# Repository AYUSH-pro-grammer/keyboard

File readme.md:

# keyboard

Custom mechanical keyboard PCB designed using KiCad.

###Motivation

I designed this device in order to get some practical experience in hardware design, PCB manufacturing, and embedded systems programming. Instead of using an off-the-shelf keyboard design, I aimed at learning all the steps required to manufacture a custom keyboard.

Working on this project, I had the opportunity to do schematic design, PCB layouting, components selection, 3D rendering, firmware writing, and manufacturing preparation with the help of KiCad. Thus, having successfully completed the whole design cycle, I got some practical experience in both hardware and software engineering.

It was my intention not only to manufacture a working device but also learn some electronics designing techniques along with problem solving in the engineering field while doing a project that is manufacturable and improvable in the future.

### Build Looks 

## Images

### Schematic

### PCB

### PCB Front 3D

### PCB Back 3D

### 3D Model 1
## Features

### 3D Model 2

---

- Custom Keyboard PCB
- Designed in KiCad
- 3D PCB Visualization
- Gerber Manufacturing Files Included

---

## Repository Structure

```text
keyboard/
│
├── code/
├── image/
├── kicad/
├── grb.zip
└── README.md
```

---

## Files

- `code/` → Firmware / keyboard code
- `image/` → PCB renders and 3D models
- `kicad/` → KiCad project files
- `grb.zip` → Gerber files for PCB manufacturing

---

## Bill of Materials

| Name | Purpose | Quantity | Avg Cost (USD) | Distributor |
|------|----------|----------|----------|----------|
| Cherry MX2A Switch Set | Key switches for typing | 1 Set | $42.00 | Keychron |
| PBT Keycap Set | Keycaps for switches | 1 Set | $13.00 | Meckeys |
| Raspberry Pi Pico | Keyboard microcontroller | 1 | $5.00 | Robu.in |
| Rotary Encoder (EC11) | Volume/media control knob | 1 | $2.00 | Robu.in |
| Encoder Knob | Mounts on rotary encoder | 1 | $1.00 | Robu.in |
| 1N4148 Diodes | Key matrix isolation | 70–100 | $3.00 | Robu.in |
| PCB Fabrication | Custom keyboard PCB | 1 | $25.00 | JLCPCB / PCBWay |
| PCB Components | Headers, sockets, passive components | 1 Lot | $5.00 | Robu.in |
| MX Hotswap Sockets (Optional) | Tool-free switch replacement | 70 | $15.00 | Meckeys / StackKB |
| USB-C Cable | Connection to computer | 1 | $3.00 | Robu.in |
| Stabilizers | Support for larger keys | 1 Set | $10.00 | Meckeys |
| Screws & Standoffs | Assembly hardware | 1 Lot | $3.00 | Local Supplier |
| 3D Printed Case | Keyboard enclosure | 1 | $20.00 | Local 3D Printing Service |
| 3D Printed Encoder Knob (Optional) | Custom encoder knob | 1 | $1.00 | Local 3D Printing Service |

## Estimated Total

**Recommended Hotswap Build Total: ~$144 USD**

## Author

Created by [AYUSH-pro-grammer](https://github.com/AYUSH-pro-grammer)

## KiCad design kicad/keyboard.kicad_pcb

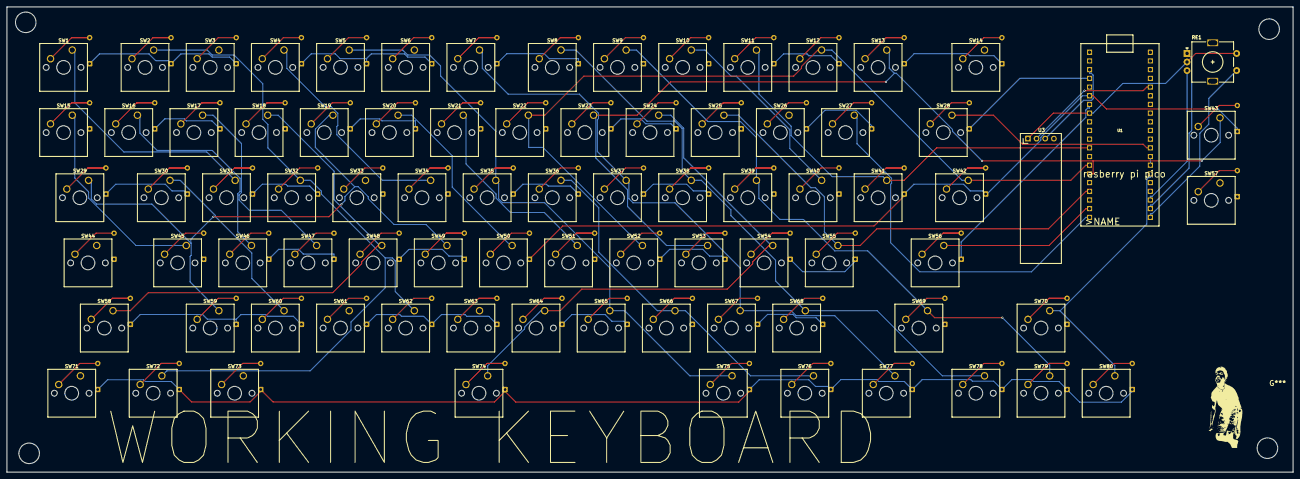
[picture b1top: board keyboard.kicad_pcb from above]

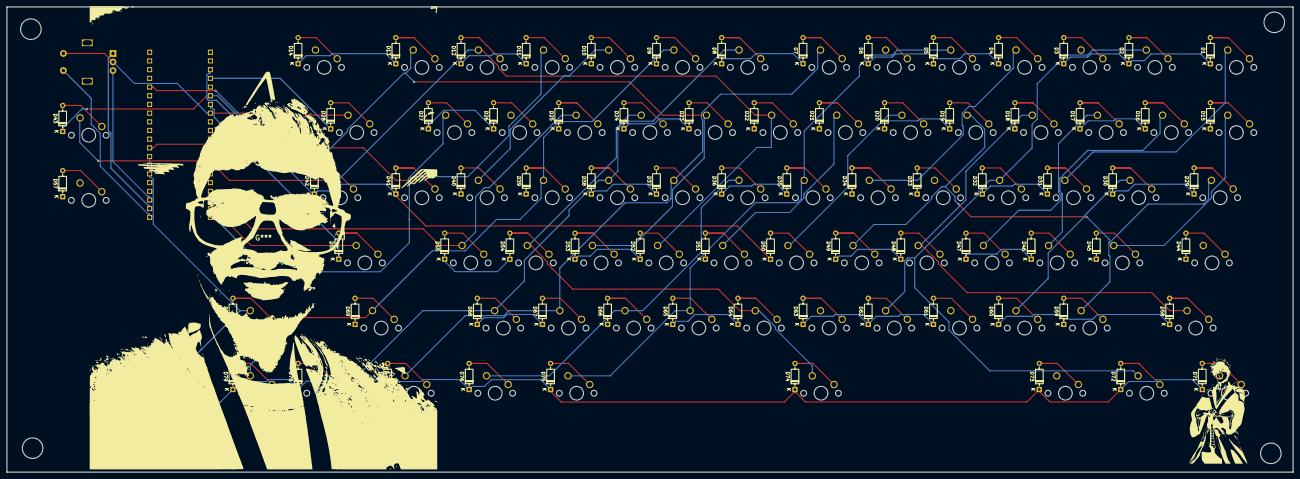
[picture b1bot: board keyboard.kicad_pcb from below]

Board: 2 copper layers, 376.0 x 136.0 mm, 164 parts (81 on the bottom side), 105 nets.

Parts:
D1, D2, D3, D4, D5, D6, D7, D8, D9, D10, D11, D12, D13, D14, D15, D16, D17, D18, D19, D20, D21, D22, D23, D24, D25, D26, D27, D28, D29, D30, D31, D32, D33, D34, D35, D36, D37, D38, D39, D40, D41, D42, D43, D44, D45, D46, D47, D48, D49, D50, D51, D52, D53, D54, D55, D56, D57, D58, D59, D60, D61, D62, D63, D64, D65, D66, D67, D68, D69, D70, D71, D72, D73, D74, D75, D76, D77, D78, D79, D80: 1N914; D_DO-35_SOD27_P7.62mm_Horizontal
RE1: RotaryEncoder_Switch; RotaryEncoder_Alps_EC11E-Switch_Vertical_H20mm
SW1, SW2, SW3, SW4, SW5, SW6, SW7, SW8, SW9, SW10, SW11, SW12, SW13, SW14, SW15, SW16, SW17, SW18, SW19, SW20, SW21, SW22, SW23, SW24, SW25, SW26, SW27, SW28, SW29, SW30, SW31, SW32, SW33, SW34, SW35, SW36, SW37, SW38, SW39, SW40, SW41, SW42, SW43, SW44, SW45, SW46, SW47, SW48, SW49, SW50, SW51, SW52, SW53, SW54, SW55, SW56, SW57, SW58, SW59, SW60, SW61, SW62, SW63, SW64, SW65, SW66, SW67, SW68, SW69, SW70, SW71, SW72, SW73, SW74, SW75, SW76, SW77, SW78, SW79, SW80: SW_SPST; SW_Cherry_MX_1.00u_PCB
U1: RASPBERRY_PI_PICO
U3: ER_OLEDM0.91_1x-I2C
i: LOGO; ichigo

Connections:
/col1: SW1.1 (A), SW11.1 (A), SW21.1 (A), SW31.1 (A), SW41.1 (A), SW51.1 (A), SW61.1 (A), SW71.1 (A), U1.GP9
/col2: SW2.1 (A), SW12.1 (A), SW22.1 (A), SW32.1 (A), SW42.1 (A), SW52.1 (A), SW62.1 (A), SW72.1 (A), U1.GP10
/col3: SW3.1 (A), SW13.1 (A), SW23.1 (A), SW33.1 (A), SW43.1 (A), SW53.1 (A), SW63.1 (A), SW73.1 (A), U1.GP11
/col4: SW4.1 (A), SW14.1 (A), SW24.1 (A), SW34.1 (A), SW44.1 (A), SW54.1 (A), SW64.1 (A), SW74.1 (A), U1.GP12
/col5: SW5.1 (A), SW15.1 (A), SW25.1 (A), SW35.1 (A), SW45.1 (A), SW55.1 (A), SW65.1 (A), SW75.1 (A), U1.GP13
/col6: SW6.1 (A), SW16.1 (A), SW26.1 (A), SW36.1 (A), SW46.1 (A), SW56.1 (A), SW66.1 (A), SW76.1 (A), U1.GP14
/col7: SW7.1 (A), SW17.1 (A), SW27.1 (A), SW37.1 (A), SW47.1 (A), SW57.1 (A), SW67.1 (A), SW77.1 (A), U1.GP15
/col8: SW8.1 (A), SW18.1 (A), SW28.1 (A), SW38.1 (A), SW48.1 (A), SW58.1 (A), SW68.1 (A), SW78.1 (A), U1.GP22
/col9: SW9.1 (A), SW19.1 (A), SW29.1 (A), SW39.1 (A), SW49.1 (A), SW59.1 (A), SW69.1 (A), SW79.1 (A), U1.GP21
/col10: SW10.1 (A), SW20.1 (A), SW30.1 (A), SW40.1 (A), SW50.1 (A), SW60.1 (A), SW70.1 (A), SW80.1 (A), U1.GP20
/encoder1: RE1.A, U1.GP17
/encoder2: RE1.B, U1.GND3
/pico3.3: U1.3V3, U3.2 (VCC)
/row1: D1.1 (K), D2.1 (K), D3.1 (K), D4.1 (K), D5.1 (K), D6.1 (K), D7.1 (K), D8.1 (K), D9.1 (K), D10.1 (K), U1.GP18
/row3: D21.1 (K), D22.1 (K), D23.1 (K), D24.1 (K), D25.1 (K), D26.1 (K), D27.1 (K), D28.1 (K), D29.1 (K), D30.1 (K), U1.GP2
/row4: D31.1 (K), D32.1 (K), D33.1 (K), D34.1 (K), D35.1 (K), D36.1 (K), D37.1 (K), D38.1 (K), D39.1 (K), D40.1 (K), U1.GP3
/row5: D41.1 (K), D42.1 (K), D43.1 (K), D44.1 (K), D45.1 (K), D46.1 (K), D47.1 (K), D48.1 (K), D49.1 (K), D50.1 (K), U1.GP4
/row6: D51.1 (K), D52.1 (K), D53.1 (K), D54.1 (K), D55.1 (K), D56.1 (K), D57.1 (K), D58.1 (K), D59.1 (K), D60.1 (K), U1.GP5
/row7: D61.1 (K), D62.1 (K), D63.1 (K), D64.1 (K), D65.1 (K), D66.1 (K), D67.1 (K), D68.1 (K), D69.1 (K), D70.1 (K), U1.GP6
/row8: D71.1 (K), D72.1 (K), D73.1 (K), D74.1 (K), D75.1 (K), D76.1 (K), D77.1 (K), D78.1 (K), D79.1 (K), D80.1 (K), U1.GP7
/scl: U1.GND4, U3.3 (SCL)
/sda: U1.GP1, U3.4 (SDA)
GND: RE1.C, RE1.S2, U1.GND5, U3.1 (GND)
unnamed: D1.2 (A), SW1.2 (B)
unnamed: D2.2 (A), SW2.2 (B)
unnamed: D3.2 (A), SW3.2 (B)
unnamed: D4.2 (A), SW4.2 (B)
unnamed: D5.2 (A), SW5.2 (B)
unnamed: D6.2 (A), SW6.2 (B)
unnamed: D7.2 (A), SW7.2 (B)
unnamed: D8.2 (A), SW8.2 (B)
unnamed: D9.2 (A), SW9.2 (B)
unnamed: D10.2 (A), SW10.2 (B)
unnamed: D11.2 (A), SW11.2 (B)
unnamed: D11.1 (K), D12.1 (K), D13.1 (K), D14.1 (K), D15.1 (K), D16.1 (K), D17.1 (K), D18.1 (K), D19.1 (K), D20.1 (K)
unnamed: D12.2 (A), SW12.2 (B)
unnamed: D13.2 (A), SW13.2 (B)
unnamed: D14.2 (A), SW14.2 (B)
unnamed: D15.2 (A), SW15.2 (B)
unnamed: D16.2 (A), SW16.2 (B)
unnamed: D17.2 (A), SW17.2 (B)
unnamed: D18.2 (A), SW18.2 (B)
unnamed: D19.2 (A), SW19.2 (B)
unnamed: D20.2 (A), SW20.2 (B)
unnamed: D21.2 (A), SW21.2 (B)
unnamed: D22.2 (A), SW22.2 (B)
unnamed: D23.2 (A), SW23.2 (B)
unnamed: D24.2 (A), SW24.2 (B)
unnamed: D25.2 (A), SW25.2 (B)
unnamed: D26.2 (A), SW26.2 (B)
unnamed: D27.2 (A), SW27.2 (B)
unnamed: D28.2 (A), SW28.2 (B)
unnamed: D29.2 (A), SW29.2 (B)
unnamed: D30.2 (A), SW30.2 (B)
unnamed: D31.2 (A), SW31.2 (B)
unnamed: D32.2 (A), SW32.2 (B)
unnamed: D33.2 (A), SW33.2 (B)
unnamed: D34.2 (A), SW34.2 (B)
unnamed: D35.2 (A), SW35.2 (B)
unnamed: D36.2 (A), SW36.2 (B)
unnamed: D37.2 (A), SW37.2 (B)
unnamed: D38.2 (A), SW38.2 (B)
unnamed: D39.2 (A), SW39.2 (B)
unnamed: D40.2 (A), SW40.2 (B)
unnamed: D41.2 (A), SW41.2 (B)
unnamed: D42.2 (A), SW42.2 (B)
unnamed: D43.2 (A), SW43.2 (B)
unnamed: D44.2 (A), SW44.2 (B)
unnamed: D45.2 (A), SW45.2 (B)
unnamed: D46.2 (A), SW46.2 (B)
unnamed: D47.2 (A), SW47.2 (B)
unnamed: D48.2 (A), SW48.2 (B)
unnamed: D49.2 (A), SW49.2 (B)
unnamed: D50.2 (A), SW50.2 (B)
unnamed: D51.2 (A), SW51.2 (B)
unnamed: D52.2 (A), SW52.2 (B)
unnamed: D53.2 (A), SW53.2 (B)
unnamed: D54.2 (A), SW54.2 (B)
unnamed: D55.2 (A), SW55.2 (B)
unnamed: D56.2 (A), SW56.2 (B)
unnamed: D57.2 (A), SW57.2 (B)
unnamed: D58.2 (A), SW58.2 (B)
unnamed: D59.2 (A), SW59.2 (B)
unnamed: D60.2 (A), SW60.2 (B)
unnamed: D61.2 (A), SW61.2 (B)
unnamed: D62.2 (A), SW62.2 (B)
unnamed: D63.2 (A), SW63.2 (B)
unnamed: D64.2 (A), SW64.2 (B)
unnamed: D65.2 (A), SW65.2 (B)
unnamed: D66.2 (A), SW66.2 (B)
unnamed: D67.2 (A), SW67.2 (B)
unnamed: D68.2 (A), SW68.2 (B)
unnamed: D69.2 (A), SW69.2 (B)
unnamed: D70.2 (A), SW70.2 (B)
unnamed: D71.2 (A), SW71.2 (B)
unnamed: D72.2 (A), SW72.2 (B)
unnamed: D73.2 (A), SW73.2 (B)
unnamed: D74.2 (A), SW74.2 (B)
unnamed: D75.2 (A), SW75.2 (B)
unnamed: D76.2 (A), SW76.2 (B)
unnamed: D77.2 (A), SW77.2 (B)
unnamed: D78.2 (A), SW78.2 (B)
unnamed: D79.2 (A), SW79.2 (B)
unnamed: D80.2 (A), SW80.2 (B)
unnamed: RE1.S1, U1.GP16

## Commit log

2026-06-12 Add Bill of Materials section to README
    Added a Bill of Materials (BOM) section with details and estimated costs.
2026-06-12 Add schematic image to README
    Added schematic image to the README.
2026-06-12 updated cad:
2026-06-12 Rename custom keyboard-bom.csv to BOM.csv
2026-06-15 Add 3D model images and features to readme
    Updated the readme to include new 3D model images and features.
